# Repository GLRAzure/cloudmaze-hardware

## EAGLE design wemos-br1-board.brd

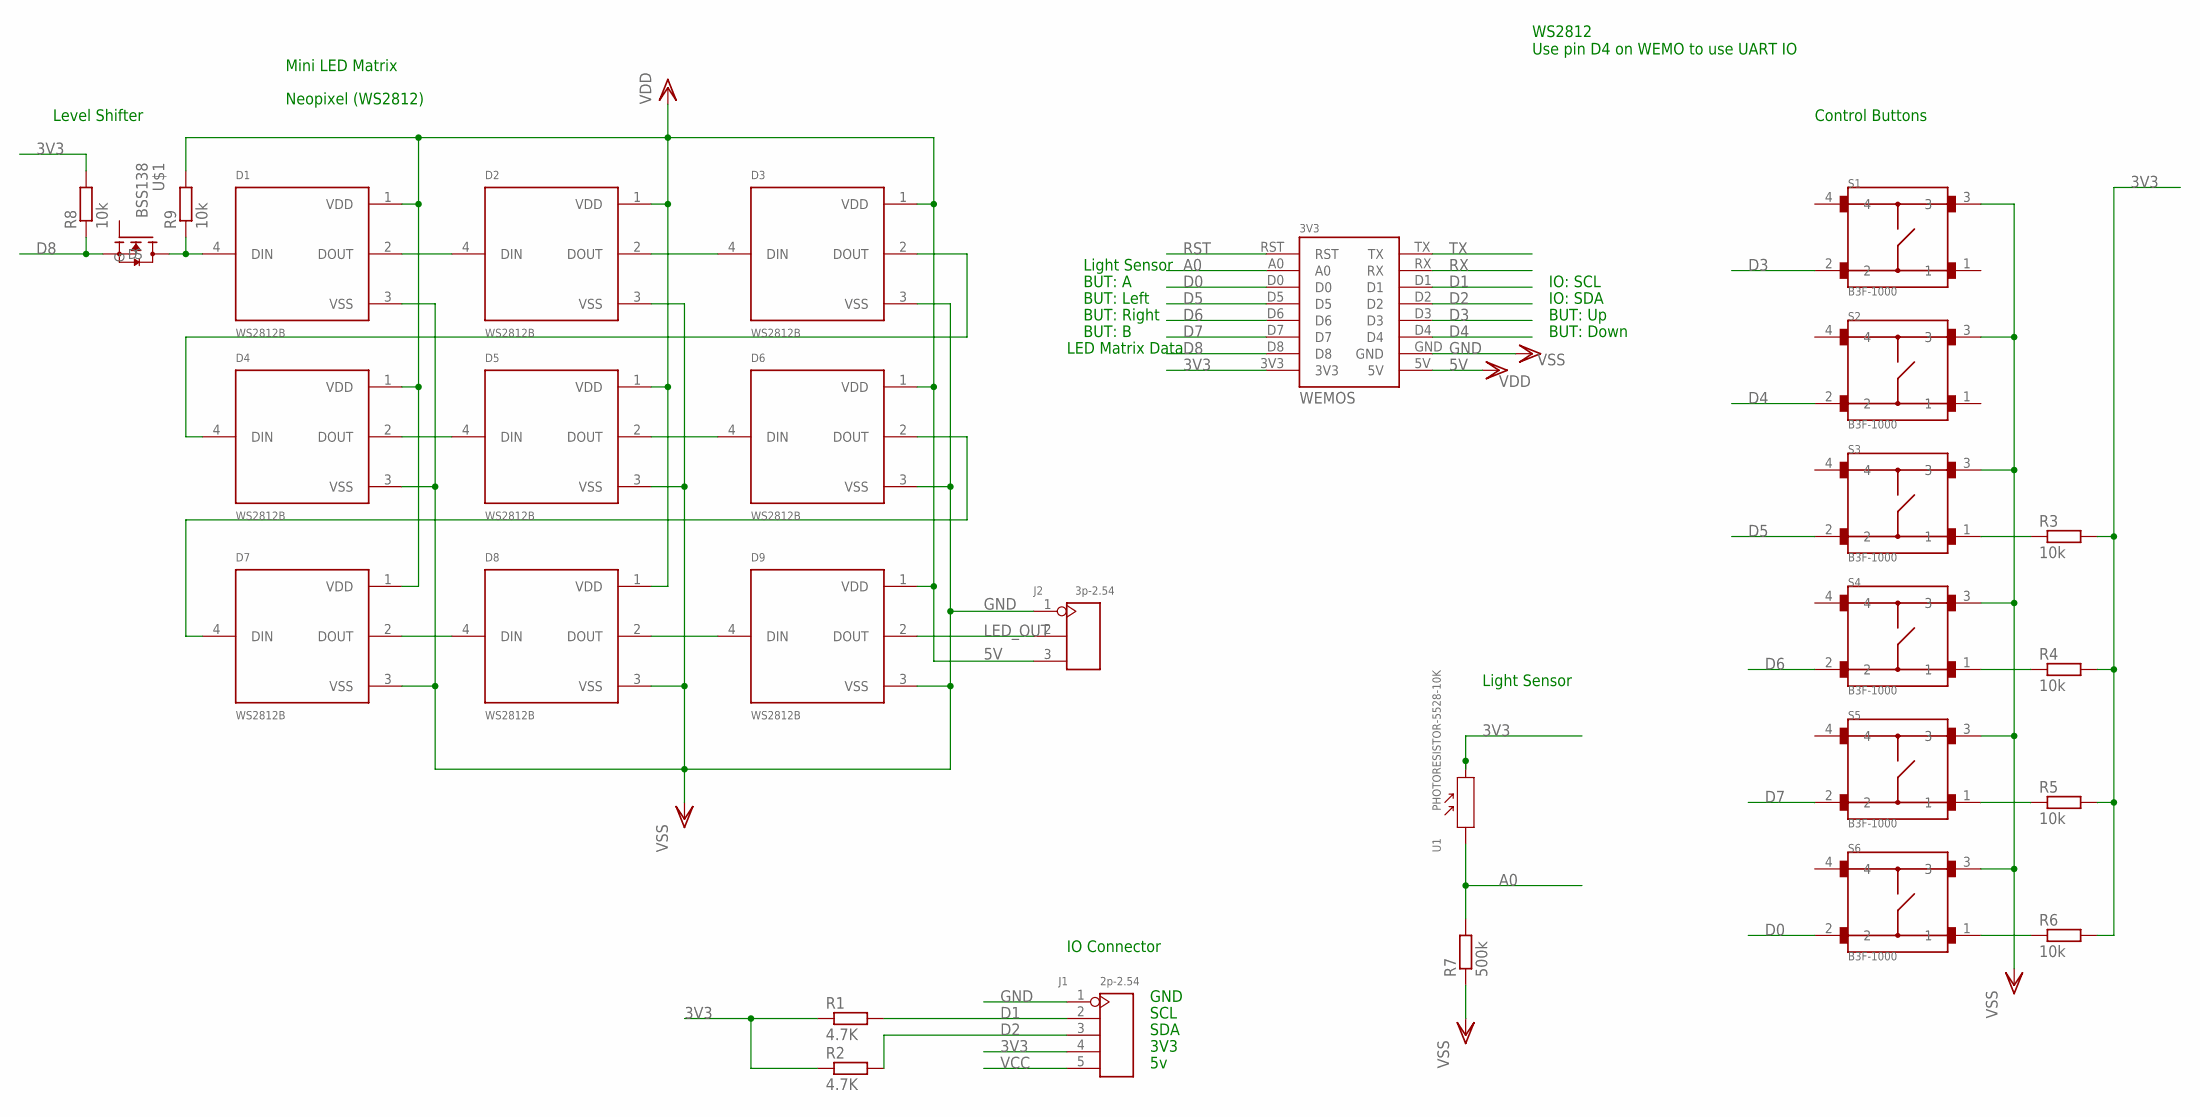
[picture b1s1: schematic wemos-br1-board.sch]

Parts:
3V3: WEMOS
D1, D2, D3, D4, D5, D6, D7, D8, D9: WS2812B; LED_WS2812B
J1: 2p-2.54; H5-2.54
J2: 3p-2.54; H3-2.54
R1, R2: 4.7K; R0805
R3, R4, R5, R6, R8, R9: 10k; R0805
R7: 500k; R0805
S1, S2, S3, S4, S5, S6: B3F-1000; SW_B3F-1000
U1: PHOTORESISTOR-5528-10K; SNR2-3.0
U$1: BSS138

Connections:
3V3: 3V3.3V3, J1.4, R1.1, R2.1, R3.2, R4.2, R5.2, R6.2, R8.2, U1.2
5V: 3V3.5V, D1.1 (VDD), D2.1 (VDD), D3.1 (VDD), D4.1 (VDD), D5.1 (VDD), D6.1 (VDD), D7.1 (VDD), D8.1 (VDD), D9.1 (VDD), J2.3, R9.2
A0: 3V3.A0, R7.2, U1.1
D0: 3V3.D0, S6.2
D1: 3V3.D1, J1.2, R1.2
D2: 3V3.D2, J1.3, R2.2
D3: 3V3.D3, S1.2
D4: 3V3.D4, S2.2
D5: 3V3.D5, S3.2
D6: 3V3.D6, S4.2
D7: 3V3.D7, S5.2
D8: 3V3.D8, R8.1, U$1.S
GND: 3V3.GND, D1.3 (VSS), D2.3 (VSS), D3.3 (VSS), D4.3 (VSS), D5.3 (VSS), D6.3 (VSS), D7.3 (VSS), D8.3 (VSS), D9.3 (VSS), J1.1, J2.1, R7.1, S1.3, S2.3, S3.3, S4.3, S5.3, S6.3
LED_OUT: D9.2 (DOUT), J2.2
unnamed: R3.1, S3.1
unnamed: D1.2 (DOUT), D2.4 (DIN)
unnamed: D2.2 (DOUT), D3.4 (DIN)
unnamed: D3.2 (DOUT), D4.4 (DIN)
unnamed: D4.2 (DOUT), D5.4 (DIN)
unnamed: D5.2 (DOUT), D6.4 (DIN)
unnamed: D6.2 (DOUT), D7.4 (DIN)
unnamed: D7.2 (DOUT), D8.4 (DIN)
unnamed: D8.2 (DOUT), D9.4 (DIN)
unnamed: R4.1, S4.1
unnamed: R5.1, S5.1
unnamed: R6.1, S6.1
unnamed: D1.4 (DIN), R9.1, U$1.D
RST: 3V3.RST
RX: 3V3.RX
TX: 3V3.TX
VCC: J1.5

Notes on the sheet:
Neopixel (WS2812)
WS2812 Use pin D4 on WEMO to use UART IO
Mini LED Matrix
Control Buttons
Light Sensor
IO Connector
Level Shifter
LED Matrix Data
IO: SDA
IO: SCL
BUT: Left
BUT: Right
BUT: Up
BUT: Down
BUT: A
BUT: B
SCL
SDA
GND
3V3

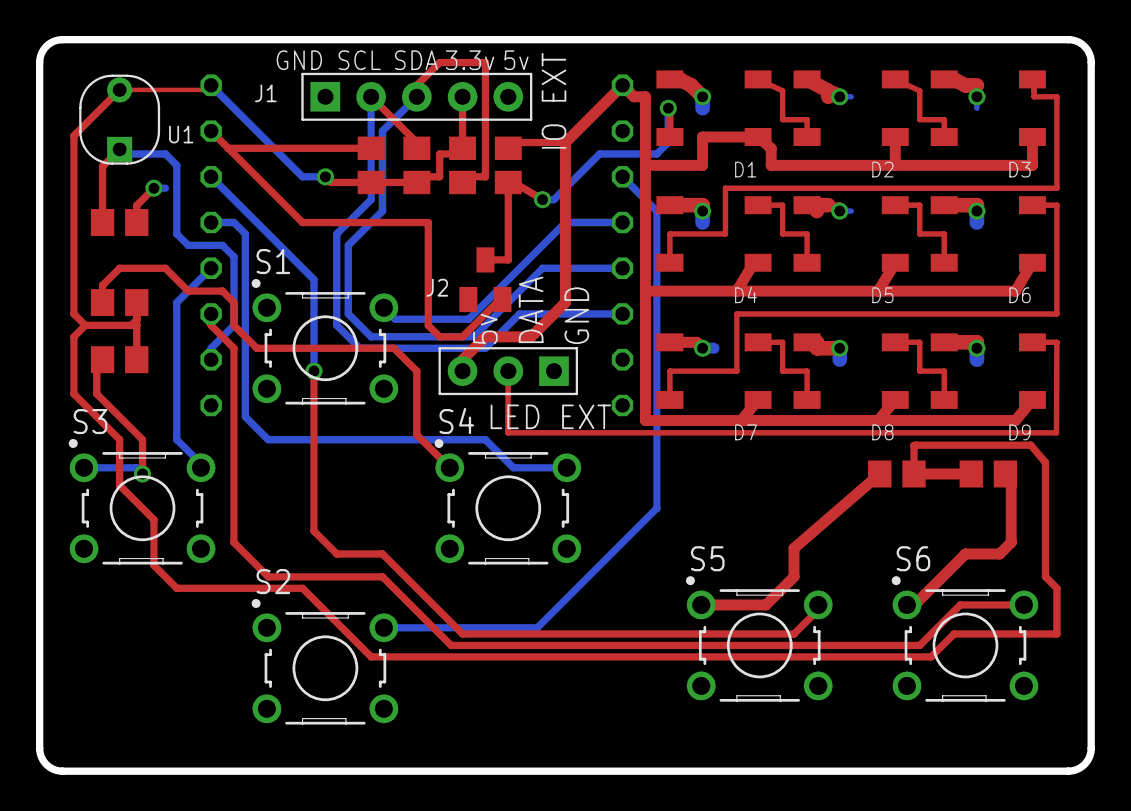
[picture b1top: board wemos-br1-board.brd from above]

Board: 2 copper layers, 58.4 x 40.6 mm, 29 parts (1 on the bottom side), 27 nets.

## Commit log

2017-01-23 First draft
2017-01-24 board fab version
2017-02-24 Deployed version
